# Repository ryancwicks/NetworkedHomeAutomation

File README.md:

# Networked Home Automation

The repo contains all the setup files for a networked home automation system based on ESPHome, Node Red and a mix of networked switches and custom firmware.

The MQTT broker and NodeRed server run on a raspberry Pi Zero W (set up with Docker).

## Raspberry Pi Setup

The system has been set up using a Raspberry Pi B+. The Raspberry Pi OS Lite was used as the base. A 7" Waveshare LCD with a capacitive touch screen is used as the main interface.

Start raspi-config, set up the wifi, change the keyboard layout and setup openssh.

I set up the user using this page: 

https://www.raspberrypi.org/documentation/configuration/security.md

I also added a lxde:

https://raspberrytips.com/upgrade-raspbian-lite-to-desktop/

In raspi-config, set the system to autologin the gui.

The final piece to add is an install of Chromium. The current version of Firefox in the apt packages doesn't support kiosk mode.

```
sudo apt install chromium
```

Copy the script run_chrome_kiosk.sh to /home/<user> and set it executable.

Copy the node-mosquitto-service.service file to /etc/systemd/system

Copy the autostart file to ~/.config/lxsession/LXDE

Copy the contents of the nodeRED directory to the ~/docker-compose directory.

Install docker: 

```
curl -sSL https://get.docker.com | sh
sudo usermod -aG docker pi 
```

Reboot here, and then test docker:

```
docker run hello-world --rm
```

```
sudo apt-get install -y libffi-dev libssl-dev
sudo apt-get install -y python3 python3-pip
sudo apt-get remove python-configparser
```

setup docker compose:

```
sudo pip3 -v install docker-compose 
```

I also installed log2ram to prevent SD card wear:

https://mcuoneclipse.com/2019/04/01/log2ram-extending-sd-card-lifetime-for-raspberry-pi-lorawan-gateway/

Set up the gui to auto login under the system preference.

Set the screensaver to return a black screen after 1 minute.

## Resolution very low

Edit the /boot/config.txt file and ensure the following is set.

max_usb_current=1
hdmi_group=2
hdmi_mode=87
hdmi_cvt 1024 600 60 6 0 0 0
hdmi_drive=1

## Chrome doesn't work:

For some reason, I was getting an illegal instruction error when I tried to run chromium. Instead I installed Midori and changed the autostart command to 

```
midori -e Fullscreen -a http://google.com
```

## Set up the backlight:

This needs to be done manually. A wire needs to be run from Raspberry pi pin 20 to a SMD pad on the board.

The RPi pin is shown here:

![images/rpi-wire.png][RPi wire location]

The other end of the wire needs to be soldered here:

![images/waveshare-wire.png][Waveshare location]

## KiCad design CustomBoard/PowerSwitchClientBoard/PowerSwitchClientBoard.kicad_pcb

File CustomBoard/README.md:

# NetworkedHomeAutomation
Simple home automation setup using ESP32's as an MQTT client and a Raspberry Pi based MQTT broker.

# Testing the client:

Install the mosquitto app:

```bash
sudo snap install mosquitto
```

In one window, open the subscriber that listens for new devices:

```bash
mosquitto_sub -t "newDevice"
```

In another window, you can turn the device on and off with 

```bash
mosquitto_pub -t "LightSwitch/power" -m "1"
```

and

```bash
mosquitto_pub -t "lightSwitch/power" -m "0"
```

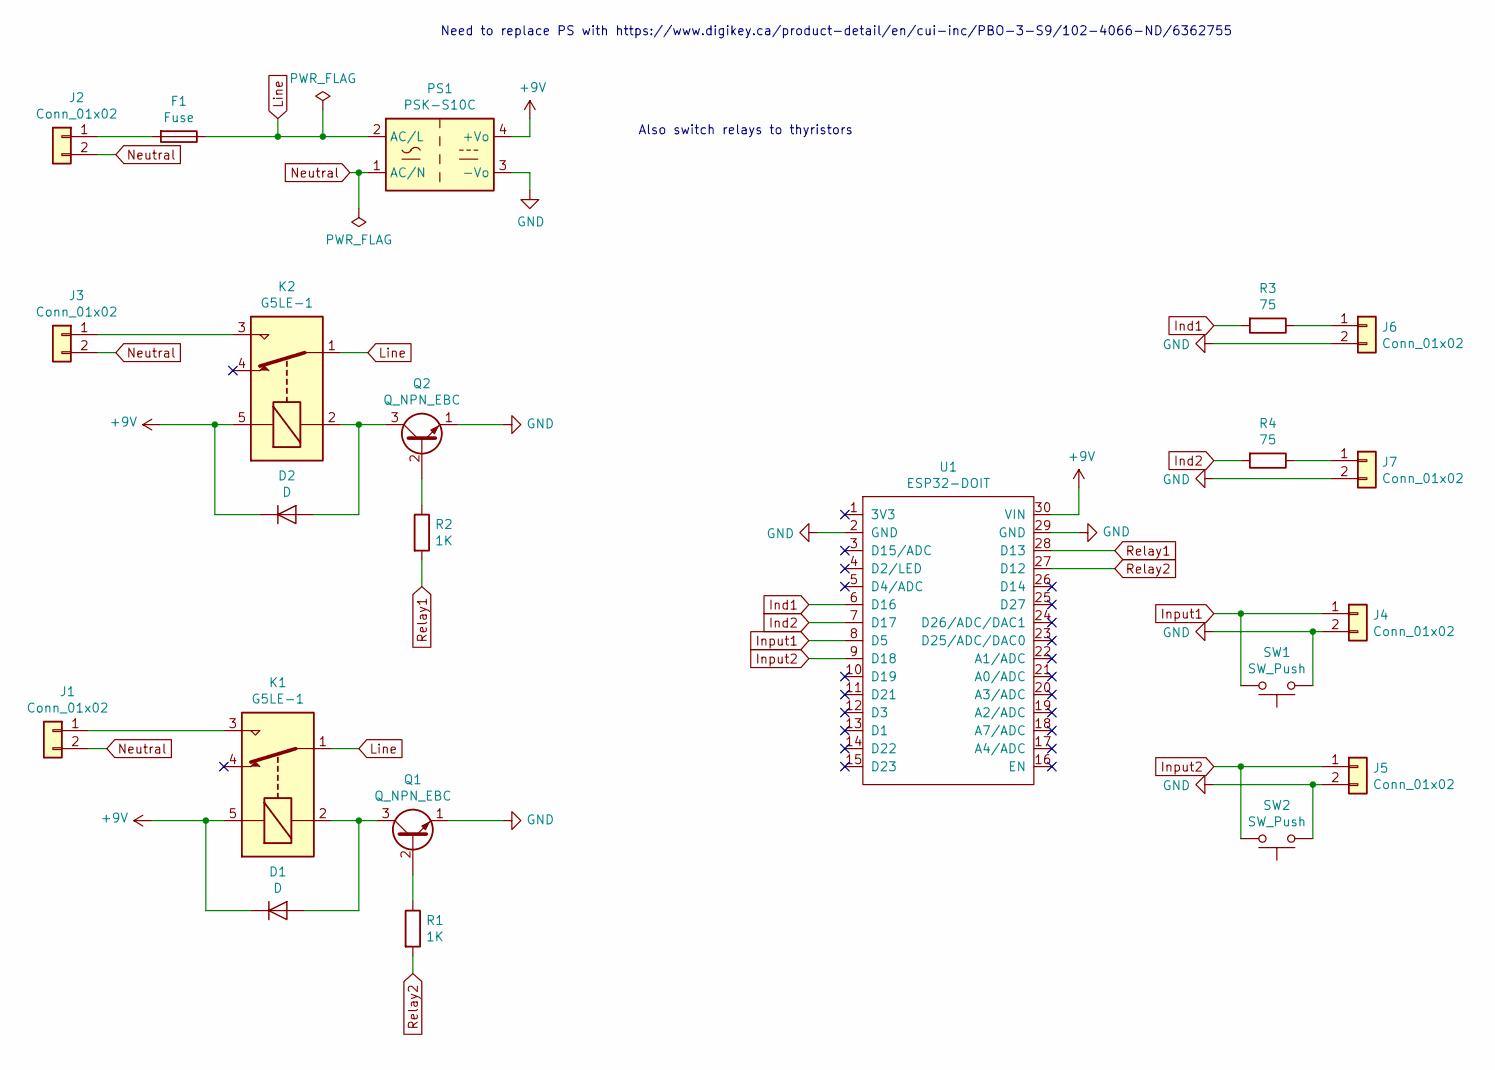
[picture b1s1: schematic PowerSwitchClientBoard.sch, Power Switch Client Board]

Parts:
D1, D2: D; D_DO-41_SOD81_P10.16mm_Horizontal; PartNumber 1N4007-TP
F1: Fuse; Fuseholder_Cylinder-5x20mm_Schurter_0031_8201_Horizontal_Op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; PartNumber Schurter 0031.8211
J1, J2, J3: Conn_01x02; SolderWirePad_1x02_P5.08mm_Drill1.5mm
J4, J5, J6, J7: Conn_01x02; PinHeader_1x02_P2.54mm_Vertical
K1, K2: G5LE-1; Relay_SPDT_Omron-G5LE-1; PartNumber G5LE-1 DC9
PS1: PSK-S10C
Q1, Q2: Q_NPN_EBC; TO-92_Inline; PartNumber PN2222ABU
R1, R2: 1K; R_Axial_DIN0207_L6.3mm_D2.5mm_P10.16mm_Horizontal; PartNumber RNF14FTD1K00
R3, R4: 75; R_Axial_DIN0207_L6.3mm_D2.5mm_P10.16mm_Horizontal; PartNumber RNF14FTD75R0
SW1, SW2: SW_Push; SW_Tactile_SKHH_Angled; PartNumber 1825027-8
U1: ESP32-DOIT; PartNumber ESP32-DOIT

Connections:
+9V: D1.1 (K), D2.1 (K), K1.5, K2.5, PS1.4 (+Vo), U1.30 (VIN)
GND: J4.2, J5.2, J6.2, J7.2, PS1.3 (-Vo), Q1.1 (E), Q2.1 (E), SW1.1, SW2.1, U1.2 (GND), U1.29 (GND)
Ind1: R3.2, U1.6 (D16)
Ind2: R4.2, U1.7 (D17)
Input1: J4.1, SW1.2, U1.8 (D5)
Input2: J5.1, SW2.2, U1.9 (D18)
Line: F1.1, K1.1, K2.1, PS1.2 (AC/L)
unnamed: D1.2 (A), K1.2, Q1.3 (C)
unnamed: D2.2 (A), K2.2, Q2.3 (C)
unnamed: F1.2, J2.1
unnamed: J1.1, K1.3
unnamed: J3.1, K2.3
unnamed: J6.1, R3.1
unnamed: J7.1, R4.1
unnamed: Q1.2 (B), R1.1
unnamed: Q2.2 (B), R2.1
Neutral: J1.2, J2.2, J3.2, PS1.1 (AC/N)
Relay1: R2.2, U1.28 (D13)
Relay2: R1.2, U1.27 (D12)

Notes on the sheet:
Need to replace PS with https://www.digikey.ca/product-detail/en/cui-inc/PBO-3-S9/102-4066-ND/6362755
Also switch relays to thyristors

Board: 2 copper layers, 22 parts (1 on the bottom side), 19 nets, no tracks yet.

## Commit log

2019-07-29 Finished Client code to turn lights on and off.
2019-08-07 Started work on mechanical and electrical. software not currently working.
2019-08-09 Started some cad work.
2020-07-13 WIP, got docker node/mqtt server working, can't get esphome devices to connect to it through mqtt.
2020-08-22 Working on Raspberry pi. Need to add setup instructions.
2020-08-26 Added documentation and some start up scripts.
